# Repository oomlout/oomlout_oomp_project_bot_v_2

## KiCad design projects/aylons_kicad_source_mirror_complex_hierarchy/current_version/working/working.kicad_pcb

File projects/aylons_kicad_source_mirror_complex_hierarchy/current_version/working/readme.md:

# kicad_source_mirror
 
## summary 
* id: aylons_kicad_source_mirror_complex_hierarchy
* user: aylons
* name: kicad_source_mirror
* board: complex_hierarchy
* repo: https://github.com/aylons/kicad-source-mirror
* src_file_repo_kicad_pcb: qa/data/complex_hierarchy.kicad_pcb
* src_file_repo_kicad_pcb_link: https://github.com/aylons/kicad-source-mirror/tree/master/qa/data/complex_hierarchy.kicad_pcb

* src_file_repo_sch: helpers/tools_to_build_newstroke-font/font.sch
* src_file_repo_sch_link: https://github.com/aylons/kicad-source-mirror/tree/master/helpers/tools_to_build_newstroke-font/font.sch
* full details link: https://github.com/oomlout/oomlout_oomp_project_bot_v_2/tree/main/projects/aylons_kicad_source_mirror_complex_hierarchy/current_version/working

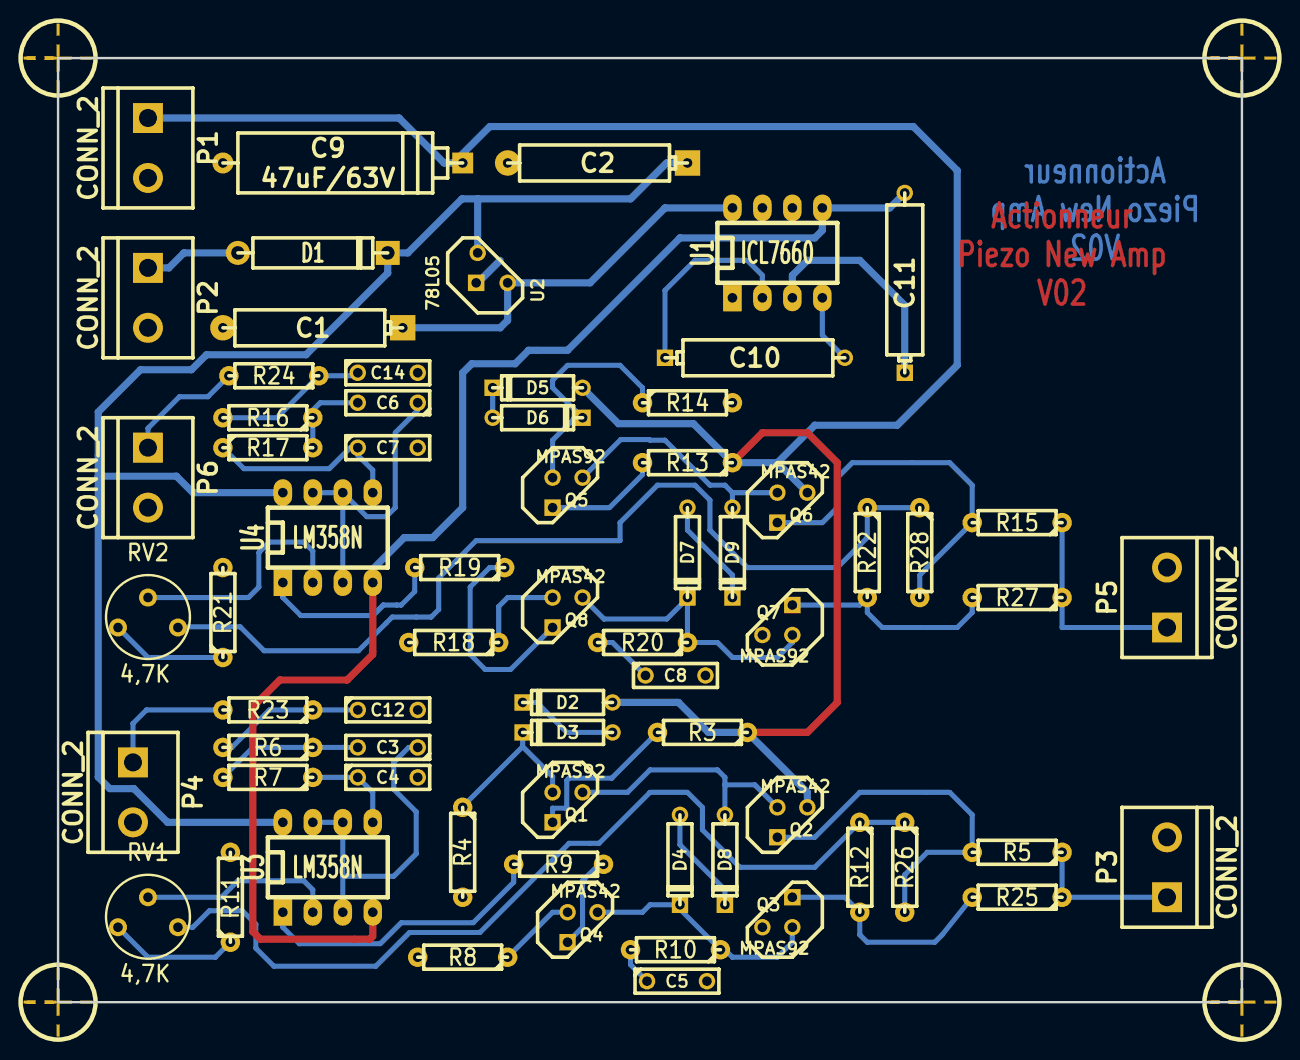
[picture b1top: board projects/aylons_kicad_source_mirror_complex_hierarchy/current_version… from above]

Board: 2 copper layers, 100.3 x 80.0 mm, 72 parts (0 on the bottom side), 50 nets.

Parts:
C1: 47uF; CP6
C2: 47uF/20V; CP6
C3, C6: 15nF; C2
C4, C7: 4,7nF; C2
C5, C8: 820pF; C2
C9: 47uF/63V; CP8
C10, C11: 10uF; CP6
C12, C14: 150nF; C2
D1: 1N4007; D5
D2, D3, D4, D5, D6, D7, D8, D9: 1N4148; D3
MIRE: *; MIRE
MIRE#2, MIRE#3, MIRE#4: *; MIRE
P1, P2, P3, P4, P5, P6: CONN_2; bornier2
Q1, Q3, Q5, Q7: MPAS92; TO92-CBE
Q2, Q4, Q6, Q8: MPAS42; TO92-CBE
R3, R13: 470; R3-LARGE_PADS
R4, R12, R14, R22, R26, R28: 220K; R3-LARGE_PADS
R5, R15, R25, R27: 47; R3-LARGE_PADS
R6, R7, R16, R17: 22K; R3-LARGE_PADS
R8, R9, R18, R19, R23, R24: 1K; R3-LARGE_PADS
R10, R20: 5,6K; R3-LARGE_PADS
R11, R21: 4,7K; R3-LARGE_PADS
RV1, RV2: 4,7K; RV2
U1: ICL7660; DIP-8__300_ELL
U2: 78L05; LM78LXX
U3, U4: LM358N; DIP-8__300_ELL

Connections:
+12V: C2.1, D1.2, U2.VI, U3.8, U4.8
-VAA: C11.2, U1.5, U3.4, U4.4
/12Vext: D1.1, P2.1
/ampli_h1: C3.1, U3.3, U3.6, U3.7
/ampli_h2: C6.1, U4.3, U4.6, U4.7
/ampli_h3: P3.1, R5.1, R25.1
/ampli_h4: P4.1, R23.2
/ampli_h5: P5.1, R15.1, R27.1
/ampli_h6: P6.1, R24.2
/ampli_h7: R12.1, R26.1, RV1.3
/ampli_h8: R22.1, R28.1, RV2.3
GND: C1.2, C2.2, C4.2, C5.2, C7.2, C8.2, C9.2, C11.1, C12.2, C14.2, P1.2, P2.2, P3.2, P4.2, P5.2, P6.2, Q3.C, Q7.C, R4.2, R8.2, R11.2, R14.2, R18.2, R21.2, U1.3, U2.GND
HT: C9.1, D2.1, D5.1, P1.1, Q2.C, Q6.C, R3.1, R13.1
unnamed: C10.2, U1.4
unnamed: C10.1, U1.2
unnamed: Q4.E, R9.1
unnamed: D2.2, D3.1
unnamed: C3.2, R6.1, R7.2
unnamed: C12.1, R6.2, R23.1
unnamed: C5.1, R10.2
unnamed: Q2.E, R5.2, R26.2
unnamed: Q3.E, R12.2, R25.2
unnamed: R11.1, RV1.1
unnamed: D3.2, Q1.B, R4.1
unnamed: Q4.B, R8.1
unnamed: R9.2, U3.1
unnamed: RV1.2, U3.2
unnamed: D4.1, D8.2
unnamed: C4.1, R7.1, U3.5
unnamed: D4.2, Q3.B, Q4.C, R10.1
unnamed: D8.1, Q1.C, Q2.B
unnamed: Q1.E, R3.2
unnamed: Q8.E, R19.1
unnamed: D5.2, D6.1
unnamed: C6.2, R16.1, R17.2
unnamed: C14.1, R16.2, R24.1
unnamed: C8.1, R20.2
unnamed: Q6.E, R15.2, R28.2
unnamed: Q7.E, R22.2, R27.2
unnamed: R21.1, RV2.1
unnamed: D6.2, Q5.B, R14.1
unnamed: Q8.B, R18.1
unnamed: R19.2, U4.1
unnamed: RV2.2, U4.2
unnamed: D7.1, D9.2
unnamed: C7.1, R17.1, U4.5
unnamed: D7.2, Q7.B, Q8.C, R20.1
unnamed: D9.1, Q5.C, Q6.B
unnamed: Q5.E, R13.2
VCC: C1.1, U1.8, U2.VO

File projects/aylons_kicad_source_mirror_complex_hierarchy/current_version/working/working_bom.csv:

"Id";"Designator";"Footprint";"Quantity";"Designation";"Supplier and ref";
1;"P1,P3,P2,P4,P5,P6";"bornier2";6;"CONN_2";;;
2;"C8,C5";"C2";2;"820pF";;;
3;"C4,C7";"C2";2;"4,7nF";;;
4;"C2";"CP6";1;"47uF/20V";;;
5;"C9";"CP8";1;"47uF/63V";;;
6;"C3,C6";"C2";2;"15nF";;;
7;"C1";"CP6";1;"47uF";;;
8;"D6,D4,D3,D2,D7,D5,D9,D8";"D3";8;"1N4148";;;
9;"D1";"D5";1;"1N4007";;;
10;"U2";"LM78LXX";1;"78L05";;;
11;"R12,R22,R4,R14,R26,R28";"R3-LARGE_PADS";6;"220K";;;
12;"R17,R6,R16,R7";"R3-LARGE_PADS";4;"22K";;;
13;"R3,R13";"R3-LARGE_PADS";2;"470";;;
14;"R18,R8,R19,R9,R23,R24";"R3-LARGE_PADS";6;"1K";;;
15;"R5,R15,R25,R27";"R3-LARGE_PADS";4;"47";;;
16;"R11,R21";"R3-LARGE_PADS";2;"4,7K";;;
17;"R10,R20";"R3-LARGE_PADS";2;"5,6K";;;
18;"Q3,Q5,Q7,Q1";"TO92-CBE";4;"MPAS92";;;
19;"Q6,Q2,Q4,Q8";"TO92-CBE";4;"MPAS42";;;
20;"U1";"DIP-8__300_ELL";1;"ICL7660";;;
21;"U4,U3";"DIP-8__300_ELL";2;"LM358N";;;
22;"RV1,RV2";"RV2";2;"4,7K";;;
23;"MIRE,MIRE,MIRE,MIRE";"MIRE";4;"*";;;
24;"C10,C11";"CP6";2;"10uF";;;
25;"C14,C12";"C2";2;"150nF";;;

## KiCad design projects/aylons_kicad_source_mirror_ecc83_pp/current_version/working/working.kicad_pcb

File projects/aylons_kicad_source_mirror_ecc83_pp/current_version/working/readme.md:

# kicad_source_mirror
 
## summary 
* id: aylons_kicad_source_mirror_ecc83_pp
* user: aylons
* name: kicad_source_mirror
* board: ecc83_pp
* repo: https://github.com/aylons/kicad-source-mirror
* src_file_repo_kicad_pcb: demos/ecc83/ecc83-pp.kicad_pcb
* src_file_repo_kicad_pcb_link: https://github.com/aylons/kicad-source-mirror/tree/master/demos/ecc83/ecc83-pp.kicad_pcb

* src_file_repo_sch: demos/ecc83/ecc83-pp.sch
* src_file_repo_sch_link: https://github.com/aylons/kicad-source-mirror/tree/master/demos/ecc83/ecc83-pp.sch
* full details link: https://github.com/oomlout/oomlout_oomp_project_bot_v_2/tree/main/projects/aylons_kicad_source_mirror_ecc83_pp/current_version/working

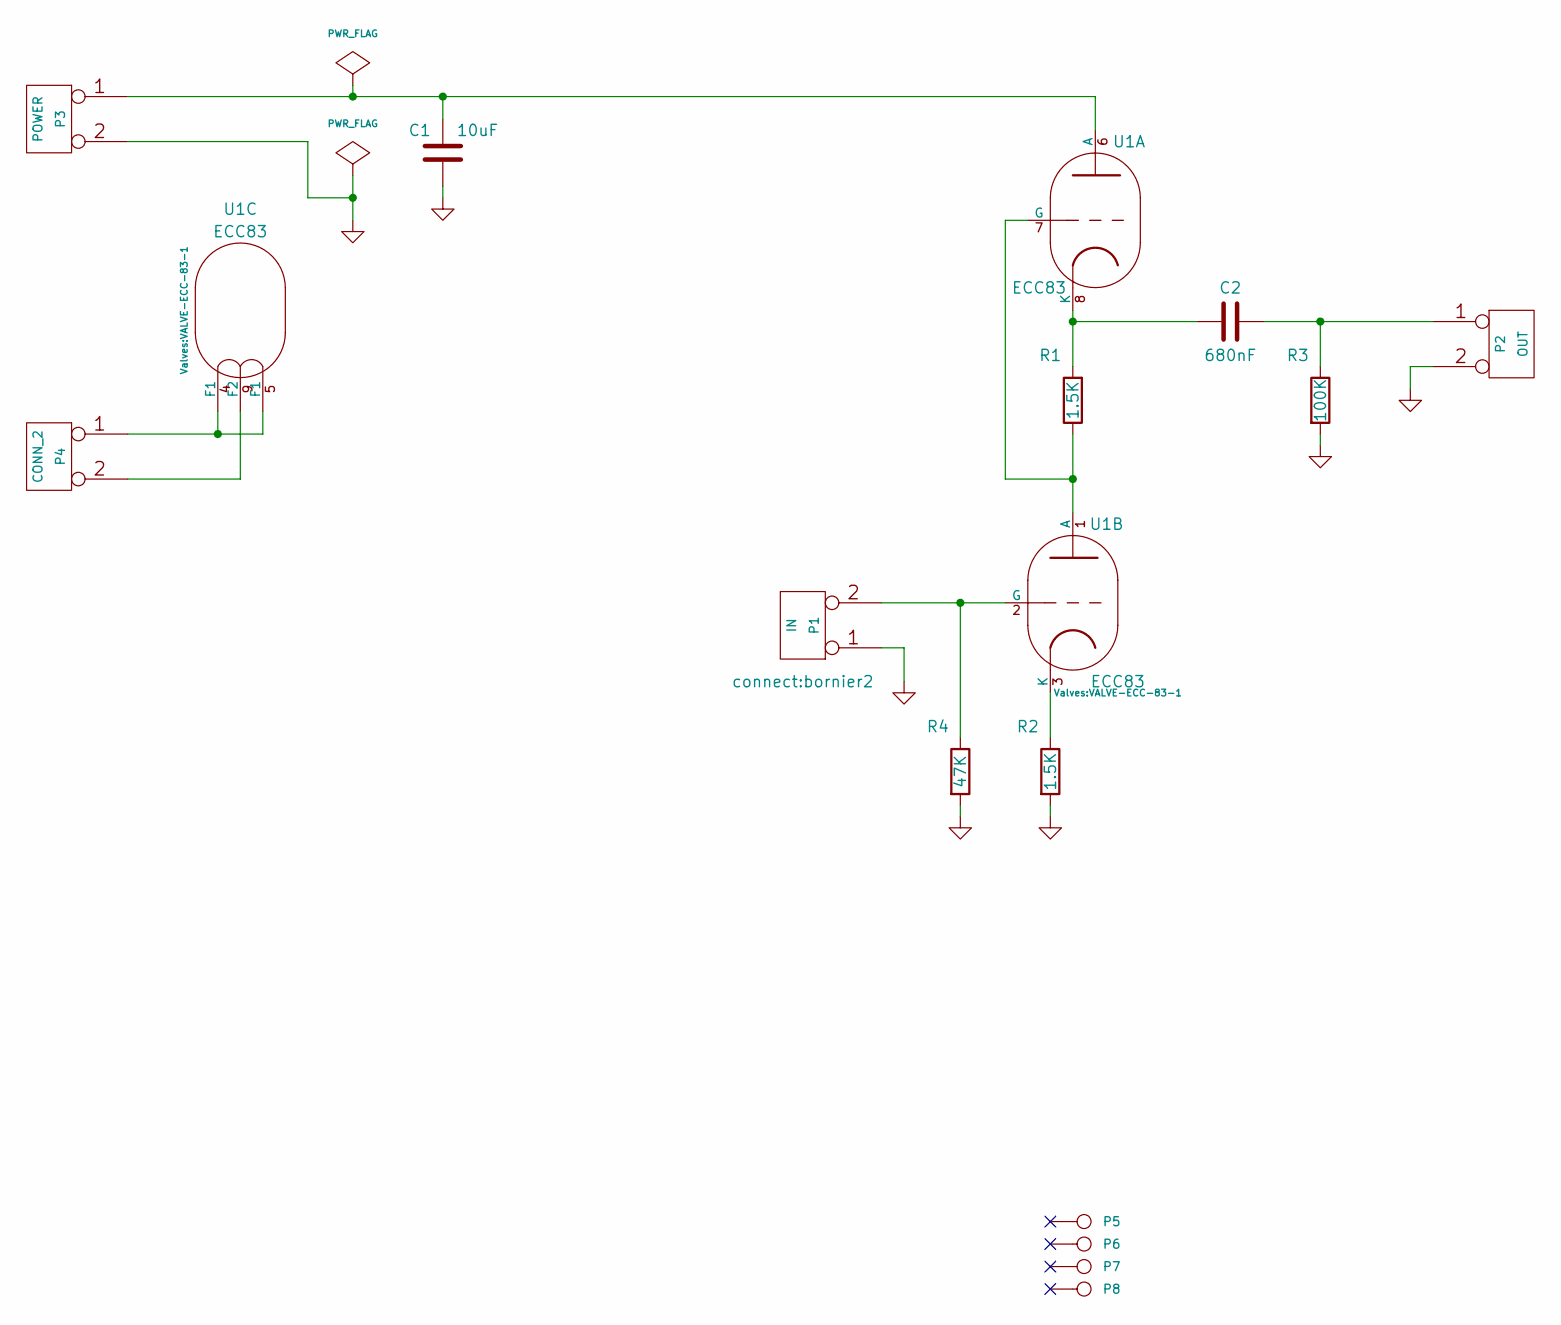
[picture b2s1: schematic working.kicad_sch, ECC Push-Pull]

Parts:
C1: 10uF; C2V10
C2: 680nF; C2
P1: IN; bornier2
P2: OUT; bornier2
P3: POWER; bornier2
P4: CONN_2; bornier2
P5, P6, P7, P8: CONN_1; 1pin
R1, R2: 1.5K; R3
R3: 100K; R3
R4: 47K; R3
U1: ECC83; VALVE-ECC-83-1

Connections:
GND: C1.2, P1.1, P2.2 (PM), P3.2 (PM), R2.2, R3.2, R4.2
unnamed: C1.1, P3.1, U1.6 (A)
unnamed: C2.1, P2.1, R3.1
unnamed: C2.2, R1.2, U1.8 (K)
unnamed: P1.2 (PM), R4.1, U1.2 (G)
unnamed: P4.1, U1.4 (F1), U1.5 (F1)
unnamed: P4.2 (PM), U1.9 (F2)
unnamed: R1.1, U1.1 (A), U1.7 (G)
unnamed: R2.1, U1.3 (K)

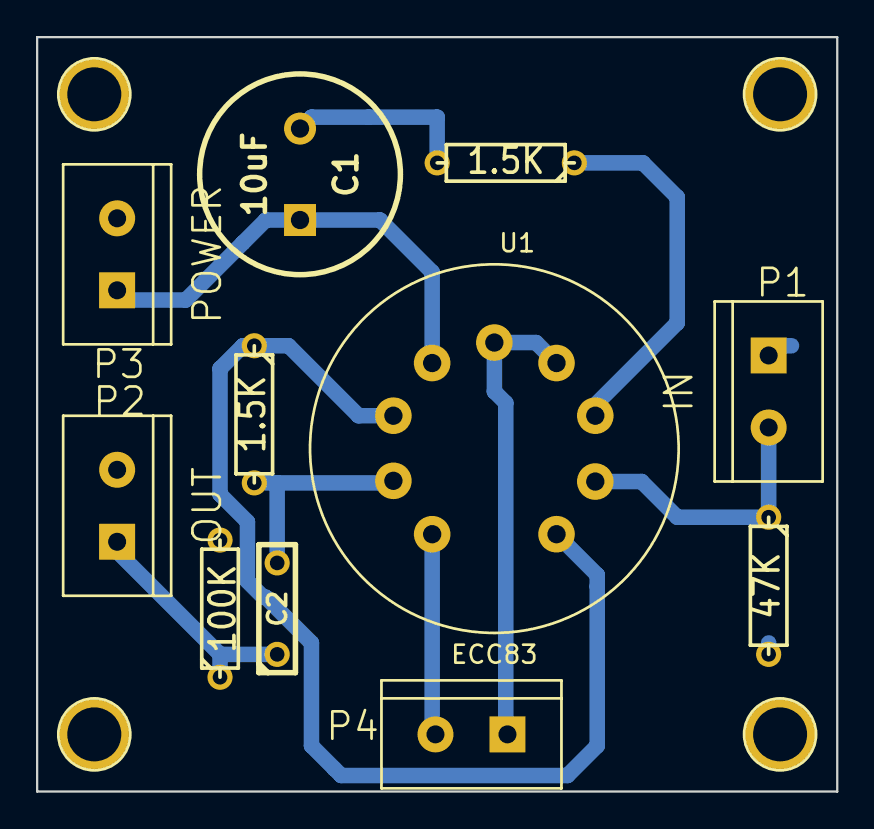
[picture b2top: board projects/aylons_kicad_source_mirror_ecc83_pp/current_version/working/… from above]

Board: 2 copper layers, 44.5 x 41.9 mm, 15 parts (0 on the bottom side), 9 nets.

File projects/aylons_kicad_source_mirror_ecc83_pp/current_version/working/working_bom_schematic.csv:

"Source:","C:\gh\oomlout_oomp_project_bot_v_2\projects\aylons_kicad_source_mirror_ecc83_pp\current_version\working\working.kicad_sch"
"Date:","27/09/2023 14:27:10"
"Tool:","Eeschema 7.0.6"
"Generator:","C:/Program Files/KiCad/7.0/bin/scripting/plugins/bom_csv_grouped_by_value_with_fp.py"
"Component Count:","15"
"Ref","Qnty","Value","Cmp name","Footprint","Description","Vendor","DNP"
"C1","1","10uF","C","discret:C2V10","","",""
"C2","1","680nF","C","discret:C2","","",""
"P1","1","IN","CONN_2","connect:bornier2","","",""
"P2","1","OUT","CONN_2","connect:bornier2","","",""
"P3","1","POWER","CONN_2","connect:bornier2","","",""
"P4","1","CONN_2","CONN_2","connect:bornier2","","",""
"P5, P6, P7, P8","4","CONN_1","CONN_1","connect:1pin","","",""
"R1, R2","2","1.5K","R","discret:R3","","",""
"R3","1","100K","R","discret:R3","","",""
"R4","1","47K","R","discret:R3","","",""
"U1","1","ECC83","ECC83","Valves:VALVE-ECC-83-1","","",""

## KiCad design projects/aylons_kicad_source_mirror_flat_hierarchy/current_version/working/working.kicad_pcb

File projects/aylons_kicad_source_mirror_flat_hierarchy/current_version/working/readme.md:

# kicad_source_mirror
 
## summary 
* id: aylons_kicad_source_mirror_flat_hierarchy
* user: aylons
* name: kicad_source_mirror
* board: flat_hierarchy
* repo: https://github.com/aylons/kicad-source-mirror
* src_file_repo_kicad_pcb: demos/flat_hierarchy/flat_hierarchy.kicad_pcb
* src_file_repo_kicad_pcb_link: https://github.com/aylons/kicad-source-mirror/tree/master/demos/flat_hierarchy/flat_hierarchy.kicad_pcb

* src_file_repo_sch: demos/flat_hierarchy/flat_hierarchy.sch
* src_file_repo_sch_link: https://github.com/aylons/kicad-source-mirror/tree/master/demos/flat_hierarchy/flat_hierarchy.sch
* full details link: https://github.com/oomlout/oomlout_oomp_project_bot_v_2/tree/main/projects/aylons_kicad_source_mirror_flat_hierarchy/current_version/working

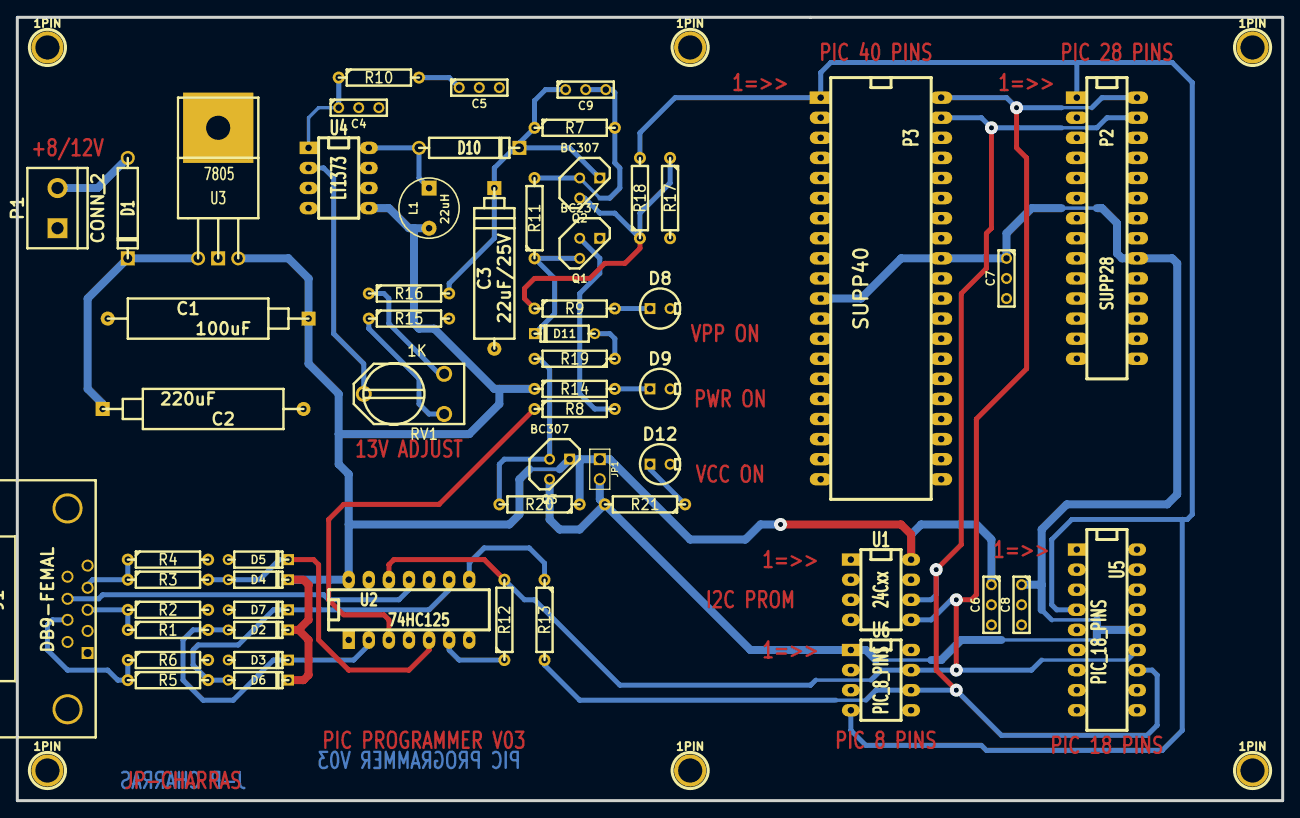
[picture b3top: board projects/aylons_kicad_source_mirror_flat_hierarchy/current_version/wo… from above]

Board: 2 copper layers, 160.0 x 99.1 mm, 64 parts (0 on the bottom side), 34 nets.

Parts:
1PIN, 1PIN#2, 1PIN#3, 1PIN#4, 1PIN#5, 1PIN#6: P***; 1pin
C1: 100uF; CP10
C2: 220uF; CP10
C3: 22uF/25V; CP8
C4: 0; C1-1
C5: 10nF; C1-1
C6, C7, C8: 100nF; C1-1
C9: 22OnF; C1-1
D1: 1N4004; D5
D2, D3, D4, D5, D6, D7, D11: BAT43; D3
D8: RED-LED; LEDV
D9: GREEN-LED; LEDV
D10: SCHOTTKY; D5
D12: YELLOW-LED; LEDV
J1: DB9-FEMAL; DB9FC
JP1: JUMPER; PIN_ARRAY_2X1
L1: 22uH; INDUCTOR_V
P1: CONN_2; bornier2
P2: SUPP28; 28DIP-ELL300
P3: SUPP40; 40DIP-ELL600
Q1: BC237; TO92
Q2, Q3: BC307; TO92
R1, R2, R3, R4, R5, R6, R7: 10K; R4
R8: 1K; R4
R9, R19, R20: 2.2K; R4
R10: 5,1K; R4
R11, R17: 22K; R4
R12, R13, R14, R21: 470; R4
R15: 6.2K; R4
R16: 62K; R4
R18: 220; R4
RV1: 1K; RV2X4
U1: 24Cxx; DIP-8__300_ELL
U2: 74HC125; DIP-14__300_ELL
U3: 7805; LM78XX
U4: LT1373; DIP-8__300_ELL
U5: PIC_18_PINS; DIP-18__300_ELL
U6: PIC_8_PINS; DIP-8__300_ELL

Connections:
/pic_programmer/CTS: J1.8, U2.11
/pic_programmer/DTR: J1.4, R3.1, R4.1
/pic_programmer/PC-CLOCK-OUT: J1.7, R5.1, R6.1
/pic_programmer/TXD: J1.3, R1.1, R2.1
CLOCK-RB6: P2.27, P3.39, R13.2, U1.6, U5.12, U6.6
DATA-RB7: P2.28, P3.40, R12.2, U1.5, U2.12, U5.13, U6.7
GND: C1.2, C2.2, C3.2, C4.2, C5.2, C6.2, C7.2, C8.2, D3.1, D5.1, D7.1, D8.2, D9.2, D12.2, J1.5, P1.1, P2.8, P2.19, P3.8, P3.12, P3.31, Q1.1, R2.2, R4.2, R6.2, R15.2, R17.2, U1.1, U1.2, U1.3, U1.4, U2.1, U2.4, U2.7, U2.10, U2.13, U3.GND, U4.6, U4.7, U5.5, U6.8
unnamed: C2.1, D1.2, U3.VI
unnamed: C4.1, R10.1, U4.1
unnamed: C5.1, R10.2
unnamed: C9.2, Q2.2, R7.2, R11.2
unnamed: D1.1, P1.2
unnamed: D2.1, D3.2, R1.2, U2.2
unnamed: D4.1, D5.2, R3.2, U2.5
unnamed: D6.1, D7.2, R5.2, U2.9
unnamed: D8.1, R9.2
unnamed: D9.1, R14.2
unnamed: D10.1, L1.1, U4.8
unnamed: D11.1, R19.1
unnamed: D11.2, Q1.3, R11.1
unnamed: D12.1, R21.1
unnamed: Q1.2, R8.2
unnamed: Q2.3, R9.1, R17.1, R18.1
unnamed: Q3.2, R19.2, R20.2
unnamed: R8.1, U2.3
unnamed: R12.1, U2.6
unnamed: R13.1, U2.8
unnamed: R15.1, RV1.1
unnamed: R16.1, RV1.3
unnamed: RV1.2, U4.2
VCC: C1.1, C6.1, D2.2, D4.2, D6.2, JP1.1, L1.2, Q3.1, R14.1, R20.1, U1.8, U2.14, U3.VO, U4.5
VCC_PIC: C7.1, C8.1, JP1.2, P2.20, P3.11, P3.32, Q3.3, R21.2, U5.14, U6.1
VPP: C3.1, C9.1, D10.2, Q2.1, R7.1, R16.2
VPP-MCLR: P2.1, P3.1, R18.2, U5.4, U6.4

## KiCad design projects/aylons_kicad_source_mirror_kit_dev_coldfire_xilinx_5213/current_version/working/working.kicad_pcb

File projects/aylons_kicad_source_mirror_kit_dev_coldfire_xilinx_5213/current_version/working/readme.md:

# kicad_source_mirror
 
## summary 
* id: aylons_kicad_source_mirror_kit_dev_coldfire_xilinx_5213
* user: aylons
* name: kicad_source_mirror
* board: kit_dev_coldfire_xilinx_5213
* repo: https://github.com/aylons/kicad-source-mirror
* src_file_repo_kicad_pcb: demos/kit-dev-coldfire-xilinx_5213/kit-dev-coldfire-xilinx_5213.kicad_pcb
* src_file_repo_kicad_pcb_link: https://github.com/aylons/kicad-source-mirror/tree/master/demos/kit-dev-coldfire-xilinx_5213/kit-dev-coldfire-xilinx_5213.kicad_pcb

* src_file_repo_sch: demos/interf_u/interf_u.sch
* src_file_repo_sch_link: https://github.com/aylons/kicad-source-mirror/tree/master/demos/interf_u/interf_u.sch
* full details link: https://github.com/oomlout/oomlout_oomp_project_bot_v_2/tree/main/projects/aylons_kicad_source_mirror_kit_dev_coldfire_xilinx_5213/current_version/working

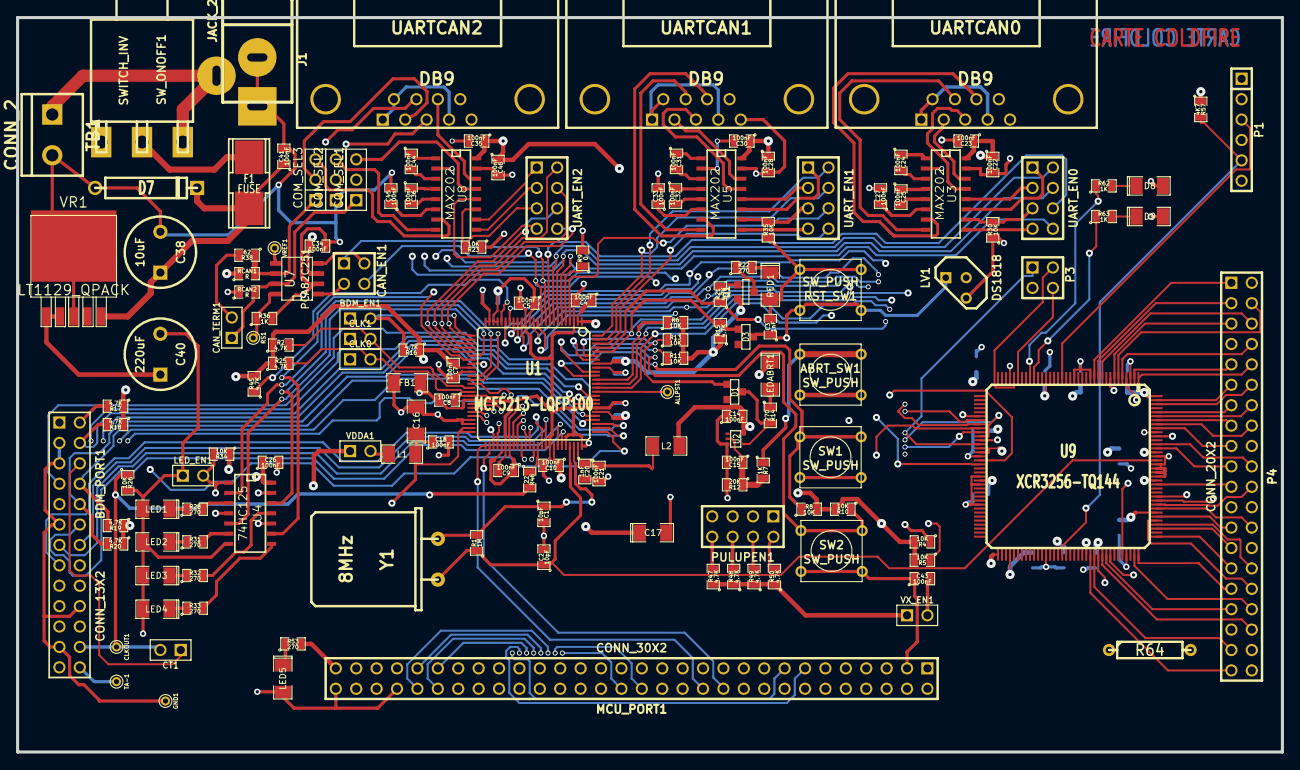
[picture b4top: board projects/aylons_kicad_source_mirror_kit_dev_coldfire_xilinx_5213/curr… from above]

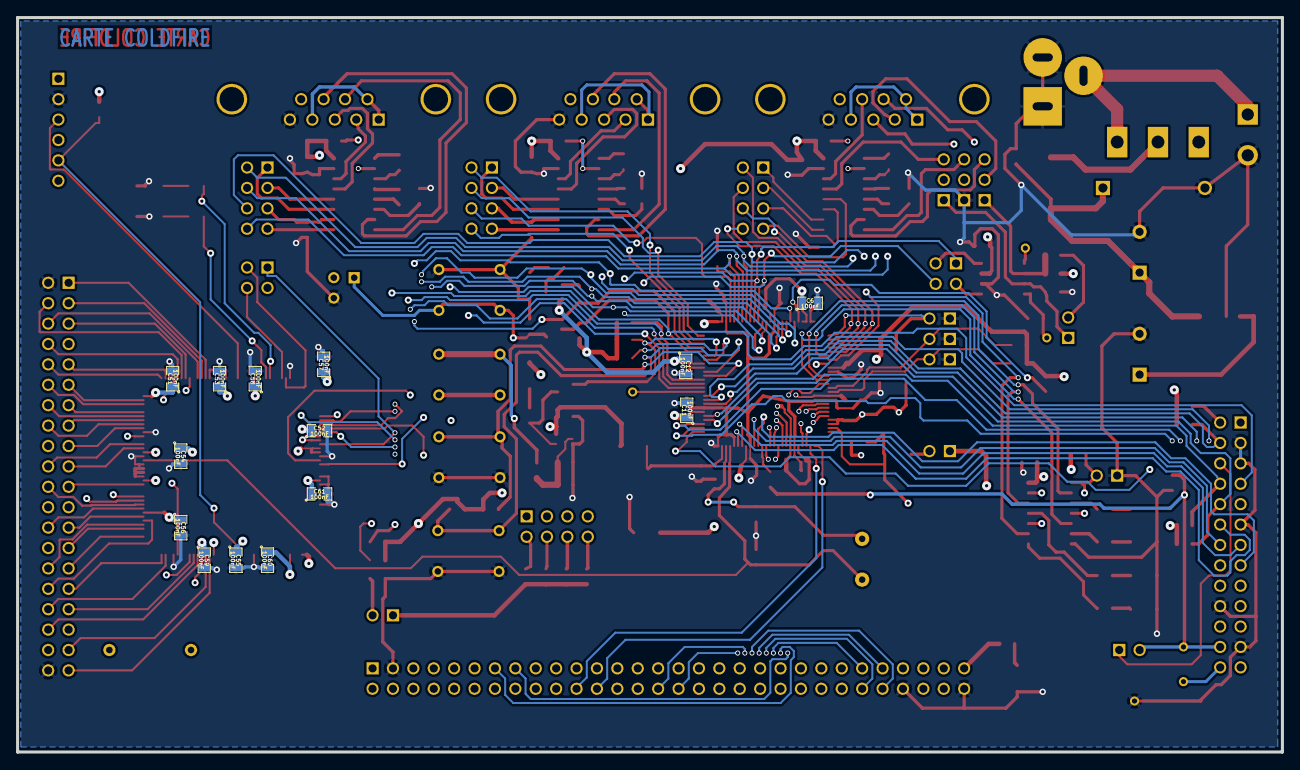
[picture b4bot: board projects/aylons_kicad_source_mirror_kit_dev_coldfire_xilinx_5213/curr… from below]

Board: 4 copper layers, 157.5 x 91.4 mm, 162 parts (14 on the bottom side), 209 nets.

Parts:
ABRT_SW1: SW_PUSH; SW_PUSH_SMALL
ALLPST1: CONN_1; PINTST
BDM_EN1: JUMPER; PIN_ARRAY_2X1
BDM_PORT1: CONN_13X2; pin_array_13x2
C1, C2: 10pF; SM0805
C3, C20: 1nF; SM0805
C4, C5, C6, C7, C8, C9, C10, C11, C12, C14, C15, C18, C21, C22, C23, C24, C25, C26, C27, C28, C30, C31, C32, C33, C34, C35, C36, C41, C43, C44, C45, C46, C51, C52, C53, C54, C55, C56, C57, C58, C59, C60, C61: 100nF; SM0805
C16: 10uF; SM1206POL
C17: 100uF; SM1206POL
C38: 10uF; C2V8
C40: 220uF; C2V8
CAN_EN1: CONN_2X2; PIN_ARRAY_2X2
CAN_TERM1: JUMPER; PIN_ARRAY_2X1
CLK0, CLK1: JUMPER; PIN_ARRAY_2X1
CLKOUT1: CONN_1; PINTST
COM_SEL1, COM_SEL2, COM_SEL3: CONN_3; PIN_ARRAY_3X1
CT1: JUMPER; PIN_ARRAY_2X1
D1, D3: BAT54; ST23AK#1
D7: 1N4004; D5
D8, D9: LED; SM1206POL
F1: FUSE; FSUPCMS
FB1: BEAD; SM1206
GND1: CONN_1; PINTST
J1: JACK_2P; JACK_ALIM
L1, L2: 10uH; SM1206
LED1, LED2, LED3, LED4, LED5: LED; SM1206POL
LEDABRT1: RED; SM1206POL
LED_EN1: JUMPER; PIN_ARRAY_2X1
LV1: DS1818; TO92-INVERT
MCU_PORT1: CONN_30X2; PIN_ARRAY_30X2
P1: CONN_6; PIN_ARRAY-6X1
P3: CONN_2X2; PIN_ARRAY_2X2
P4: CONN_20X2; PIN_ARRAY_20X2
PULUPEN1: CONN_4X2; pin_array_4x2
Q1: 3906; SOT23EBC
R1: 1M; SM0805
R2, R15, R16, R17, R18, R19, R20, R21, R25, R45, R47, R48, R49, R50: 4,7K; SM0805
R4, R5, R6, R8, R10, R11, R13, R23, R26, R30, R34, R35: 10K; SM0805
R7, R36, R62, R63: 1K; SM0805
R9: 0; SM0805
R12: 20K; SM0805
R14, R22, R28, R31, R32, R33, R53: 270; SM0805
R38: 62; SM0805
R46: 22; SM0805
R57: 4K7; SM0805
R64: 3,3; R4
RCAN1, RCAN2: R; SM0805
RED1: LED_RESET1; SM1206POL
RS1: CONN_1; PINTST
RST_SW1: SW_PUSH; SW_PUSH_SMALL
SW1, SW2: SW_PUSH; SW_PUSH_SMALL
SW_ONOFF1: SWITCH_INV; SW_SPDT
TA-1: CONN_1; PINTST
TB1: CONN_2; bornier2
U1: MCF5213-LQFP100; VQFP100
U2: 74AHC1G14; SOT353
U3, U5, U8: MAX202; SO16E
U4: 74HC125; SO14E
U7: PCA82C251; SO8E
U9: XCR3256-TQ144; TQFP144
UARTCAN0, UARTCAN1, UARTCAN2: DB9; DB9FC
UART_EN0, UART_EN1, UART_EN2: CONN_4X2; pin_array_4x2
VDDA1: JUMPER; PIN_ARRAY_2X1
VR1: LT1129_QPACK; DPAK5
VREF1: CONN_1; PINTST
VX_EN1: JUMPER; PIN_ARRAY_2X1
Y1: 8MHz; HC-18UH

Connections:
/ALLPST: ALLPST1.1, U1.86
/AN0: MCU_PORT1.10, U1.43
/AN1: MCU_PORT1.12, U1.44
/AN2: MCU_PORT1.14, U1.45
/AN3: MCU_PORT1.16, U1.46
/AN4: MCU_PORT1.18, U1.54
/AN5: MCU_PORT1.20, U1.53
/AN6: MCU_PORT1.22, U1.52
/AN7: MCU_PORT1.24, U1.51
/BKPT-: BDM_PORT1.2, R17.2, U1.76
/CLKIN/EXTAL: C1.1, R1.2, U1.73, Y1.1
/CLKMOD0: CLK0.2, R25.2, U1.40
/CLKMOD1: CLK1.2, R2.2, U1.39
/DDAT0: BDM_PORT1.19, U1.77
/DDAT1: BDM_PORT1.18, U1.78
/DDAT2: BDM_PORT1.17, U1.83
/DDAT3: BDM_PORT1.16, U1.84
/DSCLK: BDM_PORT1.4, R18.2, U1.85
/DSI: BDM_PORT1.8, R19.2, U1.79
/DSO: BDM_PORT1.10, R20.2, U1.80
/DTIN0: MCU_PORT1.34, U1.36, U4.2
/DTIN1: MCU_PORT1.36, U1.37, U4.5
/DTIN2: MCU_PORT1.38, U1.31, U4.12
/DTIN3: MCU_PORT1.40, U1.32, U4.9
/GPT0: MCU_PORT1.49, U1.58
/GPT1: MCU_PORT1.50, U1.59
/GPT2: MCU_PORT1.51, U1.61
/GPT3: MCU_PORT1.52, U1.62
/IRQ-4: MCU_PORT1.33, R8.1, SW1.1, U1.90
/IRQ-5: MCU_PORT1.35, R10.1, SW2.1, U1.91
/IRQ-6: MCU_PORT1.37, R11.1, U1.94
/IRQ-7: D1.1, MCU_PORT1.39, R13.1, U1.95
/JTAG_EN: BDM_EN1.2, R16.2, U1.26
/PST0: BDM_PORT1.15, U1.65
/PST1: BDM_PORT1.14, U1.66
/PST2: BDM_PORT1.13, U1.69
/PST3: BDM_PORT1.12, U1.70
/QSPI_CS0: MCU_PORT1.23, PULUPEN1.3, U1.20
/QSPI_CS3: MCU_PORT1.29, U1.12
/TCLK: BDM_PORT1.24, CLKOUT1.1, CT1.2, R26.1, R46.2
/VDDPLL: C20.1, C21.1, L2.2, U1.74
/inout_user/CANRX: CAN_EN1.4, MCU_PORT1.28, PULUPEN1.7, U1.11
/inout_user/CANTX: CAN_EN1.1, MCU_PORT1.26, PULUPEN1.5, U1.10
/inout_user/CAN_H: CAN_TERM1.1, COM_SEL1.1, RCAN2.2, U7.7
/inout_user/CAN_L: COM_SEL3.1, R38.1, RCAN1.2, U7.6
/inout_user/CTS0: U3.8, UARTCAN0.7
/inout_user/CTS1: U5.8, UARTCAN1.7
/inout_user/CTS2/CANH: COM_SEL1.2, UARTCAN2.7
/inout_user/PWM1: MCU_PORT1.13, U1.38
/inout_user/PWM3: MCU_PORT1.15, U1.33
/inout_user/PWM5: MCU_PORT1.30, U1.60
/inout_user/PWM7: MCU_PORT1.32, U1.63
/inout_user/QSPI_DIN: MCU_PORT1.19, U1.16, U9.46
/inout_user/QSPI_DOUT: MCU_PORT1.17, U1.17, U9.47
/inout_user/QSPI_SCLK: MCU_PORT1.21, PULUPEN1.1, U1.18, U9.48
/inout_user/RCON-: MCU_PORT1.53, R45.1, U1.21
/inout_user/RSTI-: BDM_PORT1.7, D3.1, MCU_PORT1.6, R15.2, U1.96
/inout_user/RTS0: U3.7, UARTCAN0.8
/inout_user/RTS0-: MCU_PORT1.4, R21.1, U1.97
/inout_user/RTS1: U5.7, UARTCAN1.8
/inout_user/RTS2: U8.14, UARTCAN2.8
/inout_user/RXD0: U3.13, UARTCAN0.3
/inout_user/RXD1: U5.13, UARTCAN1.3
/inout_user/RXD2: COM_SEL2.2, UARTCAN2.3
/inout_user/RxD_CAN: CAN_EN1.2, U7.4
/inout_user/TXD0: U3.14, UARTCAN0.2
/inout_user/TXD1: U5.14, UARTCAN1.2
/inout_user/TXD2/CANL: COM_SEL3.2, UARTCAN2.2
/inout_user/TxD_CAN: CAN_EN1.3, U7.1
/inout_user/UCTS0: MCU_PORT1.44, U1.6, UART_EN0.8
/inout_user/UCTS1: MCU_PORT1.11, P3.1, U1.98, U9.49, UART_EN1.8
/inout_user/UCTS2: MCU_PORT1.48, U1.27, UART_EN2.8
/inout_user/URTS0: MCU_PORT1.42, U1.9, UART_EN0.6
/inout_user/URTS1: MCU_PORT1.9, P3.3, U1.4, U9.53, UART_EN1.6
/inout_user/URTS2: MCU_PORT1.46, U1.30, UART_EN2.6
/inout_user/URXD0: MCU_PORT1.43, U1.7, UART_EN0.4
/inout_user/URXD1: MCU_PORT1.7, U1.100, UART_EN1.4
/inout_user/URXD2: MCU_PORT1.47, U1.28, UART_EN2.4
/inout_user/UTXD0: MCU_PORT1.41, U1.8, UART_EN0.2
/inout_user/UTXD1: MCU_PORT1.5, U1.99, UART_EN1.2
/inout_user/UTXD2: MCU_PORT1.45, U1.29, UART_EN2.2
/inout_user/VCCA: C16.1, C18.1, L1.2, MCU_PORT1.55, MCU_PORT1.57, U1.49, U1.50
/xilinx/+3,3V_OUT: P4.38, R64.2
/xilinx/GLCK2: C2.1, R1.1, U1.72, U9.128, Y1.2
/xilinx/IRQ-1: MCU_PORT1.2, R4.1, U1.87, U9.42
/xilinx/IRQ-2: MCU_PORT1.8, R5.1, U1.88, U9.43
/xilinx/IRQ-3: MCU_PORT1.31, R6.1, U1.89, U9.44
/xilinx/LED_TEST1: R62.1, U9.28
/xilinx/LED_TEST2: R63.1, U9.27
/xilinx/QSPI_CS1: MCU_PORT1.25, U1.19, U9.54
/xilinx/QSPI_CS2: MCU_PORT1.27, U1.13, U9.45
/xilinx/TCK: P1.5, R57.2, U9.89
/xilinx/TDI: P1.4, U9.4
/xilinx/TDO: P1.6, U9.104
/xilinx/TMS: P1.3, U9.20
/xilinx/XIL_D0: P4.1, U9.12
/xilinx/XIL_D1: P4.3, U9.11
/xilinx/XIL_D2: P4.5, U9.7
/xilinx/XIL_D3: P4.7, U9.8
/xilinx/XIL_D4: P4.9, U9.2
/xilinx/XIL_D5: P4.11, U9.143
/xilinx/XIL_D6: P4.13, U9.140
/xilinx/XIL_D7: P4.15, U9.138
/xilinx/XIL_D8: P4.17, U9.136
/xilinx/XIL_D9: P4.19, U9.131
/xilinx/XIL_D10: P4.21, U9.122
/xilinx/XIL_D11: P4.23, U9.119
/xilinx/XIL_D12: P4.25, U9.114
/xilinx/XIL_D13: P4.27, U9.111
/xilinx/XIL_D14: P4.29, U9.109
/xilinx/XIL_D15: P4.31, U9.108
/xilinx/XIL_D16: P4.33, U9.100
/xilinx/XIL_D17: P4.35, U9.101
/xilinx/XIL_D18: P4.37, U9.97
/xilinx/XIL_D19: P4.39, U9.96
/xilinx/XIL_D20: P4.4, U9.6
/xilinx/XIL_D21: P4.6, U9.10
/xilinx/XIL_D22: P4.8, U9.5
/xilinx/XIL_D23: P4.10, U9.1
/xilinx/XIL_D24: P4.12, U9.142
/xilinx/XIL_D25: P4.14, U9.139
/xilinx/XIL_D26: P4.16, U9.137
/xilinx/XIL_D27: P4.18, U9.134
/xilinx/XIL_D28: P4.20, U9.132
/xilinx/XIL_D29: P4.22, U9.117
/xilinx/XIL_D30: P4.24, U9.118
/xilinx/XIL_D31: P4.26, U9.116
/xilinx/XIL_D32: P4.28, U9.98
/xilinx/XIL_D33: P4.30, U9.112
/xilinx/XIL_D34: P4.32, U9.113
/xilinx/XIL_D35: P4.34, U9.107
/xilinx/XIL_D36: P4.36, U9.99
GND: BDM_EN1.1, BDM_PORT1.3, BDM_PORT1.5, BDM_PORT1.11, BDM_PORT1.20, BDM_PORT1.23, C1.2, C2.2, C3.2, C4.2, C5.2, C6.2, C7.2, C8.2, C9.2, C10.2, C11.2, C12.2, C14.1, C15.2, C17.2, C20.2, C21.2, C22.2, C26.2, C27.2, C28.2, C33.2, C34.2, C38.2, C40.2, C41.2, C43.1, C45.2, C46.2, C51.2, C52.2, C53.2, C54.2, C55.2, C56.2, C57.2, C58.2, C59.2, C60.2, C61.2, CLK0.1, CLK1.1, COM_SEL2.1, D7.1, D8.2, D9.2, FB1.1, GND1.1, J1.1, J1.2, LED1.2, LED2.2, LED3.2, LED4.2, LED5.2, LED_EN1.1, LV1.3, MCU_PORT1.3, MCU_PORT1.54, MCU_PORT1.60, P1.2, P4.2, P4.40, R9.2, R12.2, R23.1, R26.2, R30.1, R35.1, R36.2, RCAN2.1, RED1.2, RST_SW1.2, SW1.2, SW2.2, TB1.2, U1.3, U1.15, U1.24, U1.25, U1.35, U1.42, U1.56, U1.67, U1.71, U1.75, U1.82, U1.92, U2.3, U3.15, U4.7, U5.15, U7.2, U8.15, U9.3, U9.13, U9.17, U9.33, U9.52, U9.57, U9.59, U9.64, U9.85, U9.105, U9.124, U9.125, U9.126, U9.127, U9.129, U9.135, UARTCAN0.5, UARTCAN1.5, UARTCAN2.5, VR1.3
GNDA: C16.2, C18.2, FB1.2, MCU_PORT1.56, MCU_PORT1.58, U1.47, U1.48
unnamed: ABRT_SW1.1, R7.1
unnamed: BDM_PORT1.6, CT1.1
unnamed: BDM_PORT1.26, TA-1.1
unnamed: C3.1, D3.2, LV1.1, RST_SW1.1
unnamed: C15.1, R7.2, R12.1, U2.2
unnamed: C23.2, U3.2
unnamed: C24.1, U3.1
unnamed: C24.2, U3.3
unnamed: C25.1, U3.4
unnamed: C25.2, U3.5
unnamed: C27.1, U3.6
unnamed: C30.2, U5.2
unnamed: C31.1, U5.1
unnamed: C31.2, U5.3
unnamed: C32.1, U5.4
unnamed: C32.2, U5.5
unnamed: C33.1, U5.6
unnamed: C35.2, U8.2
unnamed: C36.1, U8.4
unnamed: C36.2, U8.5
unnamed: C38.1, C41.1, D7.2, F1.2, VR1.5
unnamed: C43.2, MCU_PORT1.1, VX_EN1.2
unnamed: C44.1, U8.1
unnamed: C44.2, U8.3
unnamed: C45.1, U8.6
unnamed: CAN_TERM1.2, R38.2
unnamed: COM_SEL1.3, U8.13
unnamed: COM_SEL2.3, U8.8
unnamed: COM_SEL3.3, U8.7
unnamed: D1.2, R14.2, U2.4
unnamed: D8.1, R62.2
unnamed: D9.1, R63.2
unnamed: F1.1, SW_ONOFF1.2
unnamed: J1.3, SW_ONOFF1.3, TB1.1
unnamed: L1.1, VDDA1.2
unnamed: LED1.1, R28.1
unnamed: LED2.1, R31.1
unnamed: LED3.1, R32.1
unnamed: LED4.1, R33.1
unnamed: LED5.1, R53.1
unnamed: LEDABRT1.2, R14.1
unnamed: LED_EN1.2, R34.2, U4.1, U4.4, U4.10, U4.13
unnamed: P3.2, U9.32
unnamed: P3.4, U9.31
unnamed: PULUPEN1.2, R50.2
unnamed: PULUPEN1.4, R49.2
unnamed: PULUPEN1.6, R48.2
unnamed: PULUPEN1.8, R47.2
unnamed: Q1.2, R21.2
unnamed: Q1.3, R22.1
unnamed: R9.1, U1.5
unnamed: R22.2, RED1.1
unnamed: R23.2, U8.11, UART_EN2.5
unnamed: R28.2, U4.3
unnamed: R30.2, U3.10, UART_EN0.5
unnamed: R31.2, U4.6
unnamed: R32.2, U4.11
unnamed: R33.2, U4.8
unnamed: R35.2, U5.10, UART_EN1.5
unnamed: R36.1, RS1.1, U7.8
unnamed: R46.1, U1.64
unnamed: U3.9, UART_EN0.7
unnamed: U3.11, UART_EN0.1
unnamed: U3.12, UART_EN0.3
unnamed: U5.9, UART_EN1.7
unnamed: U5.11, UART_EN1.1
unnamed: U5.12, UART_EN1.3
unnamed: U7.5, VREF1.1
unnamed: U8.9, UART_EN2.3
unnamed: U8.10, UART_EN2.1
unnamed: U8.12, UART_EN2.7
unnamed: UARTCAN0.1, UARTCAN0.4, UARTCAN0.6
unnamed: UARTCAN1.1, UARTCAN1.4, UARTCAN1.6
unnamed: UARTCAN2.1, UARTCAN2.4, UARTCAN2.6
VDD: ABRT_SW1.2, BDM_PORT1.9, BDM_PORT1.25, C4.1, C5.1, C6.1, C7.1, C8.1, C9.1, C10.1, C11.1, C12.1, C14.2, C17.1, C22.1, C23.1, C26.1, C28.1, C30.1, C34.1, C35.1, C40.1, C46.1, C51.1, C52.1, C53.1, C54.1, C55.1, C56.1, C57.1, C58.1, C59.1, C60.1, C61.1, L2.1, LEDABRT1.1, LV1.2, MCU_PORT1.59, P1.1, Q1.1, R2.1, R4.2, R5.2, R6.2, R8.2, R10.2, R11.2, R13.2, R15.1, R16.1, R17.1, R18.1, R19.1, R20.1, R25.1, R34.1, R45.2, R47.1, R48.1, R49.1, R50.1, R53.2, R57.1, R64.1, RCAN1.1, U1.1, U1.2, U1.14, U1.22, U1.23, U1.34, U1.41, U1.55, U1.57, U1.68, U1.81, U1.93, U2.5, U3.16, U4.14, U5.16, U7.3, U8.16, U9.24, U9.50, U9.51, U9.58, U9.73, U9.76, U9.95, U9.115, U9.123, U9.130, U9.144, VDDA1.1, VR1.1, VR1.2, VX_EN1.1

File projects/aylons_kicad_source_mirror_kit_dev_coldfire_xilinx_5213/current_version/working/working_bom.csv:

"Id";"Designator";"Footprint";"Quantity";"Designation";"Supplier and ref";
1;"ABRT_SW1,RST_SW1,SW1,SW2";"SW_PUSH_SMALL";4;"SW_PUSH";;;
2;"ALLPST1,CLKOUT1,GND1,RS1,TA-1,VREF1";"PINTST";6;"CONN_1";;;
3;"BDM_EN1,CAN_TERM1,CLK0,CLK1,CT1,LED_EN1,VDDA1,VX_EN1";"PIN_ARRAY_2X1";8;"JUMPER";;;
4;"BDM_PORT1";"pin_array_13x2";1;"CONN_13X2";;;
5;"C1,C2";"SM0805";2;"10pF";;;
6;"C3,C20";"SM0805";2;"1nF";;;
7;"C4,C5,C7,C8,C9,C10,C14,C15,C18,C21,C22,C23,C24,C25,C26,C27,C28,C30,C31,C32,C33,C34,C35,C36,C41,C43,C44,C45,C46,C6,C11,C12,C51,C52,C53,C54,C55,C56,C57,C58,C59,C60,C61";"SM0805";43;"100nF";;;
8;"C16";"SM1206POL";1;"10uF";;;
9;"C17";"SM1206POL";1;"100uF";;;
10;"C38";"C2V8";1;"10uF";;;
11;"C40";"C2V8";1;"220uF";;;
12;"CAN_EN1,P3";"PIN_ARRAY_2X2";2;"CONN_2X2";;;
13;"COM_SEL1,COM_SEL2,COM_SEL3";"PIN_ARRAY_3X1";3;"CONN_3";;;
14;"D1,D3";"ST23AK#1";2;"BAT54";;;
15;"D7";"D5";1;"1N4004";;;
16;"D8,D9,LED1,LED2,LED3,LED4,LED5";"SM1206POL";7;"LED";;;
17;"F1";"FSUPCMS";1;"FUSE";;;
18;"FB1";"SM1206";1;"BEAD";;;
19;"J1";"JACK_ALIM";1;"JACK_2P";;;
20;"L1,L2";"SM1206";2;"10uH";;;
21;"LEDABRT1";"SM1206POL";1;"RED";;;
22;"LV1";"TO92-INVERT";1;"DS1818";;;
23;"MCU_PORT1";"PIN_ARRAY_30X2";1;"CONN_30X2";;;
24;"P1";"PIN_ARRAY-6X1";1;"CONN_6";;;
25;"P4";"PIN_ARRAY_20X2";1;"CONN_20X2";;;
26;"PULUPEN1,UART_EN0,UART_EN1,UART_EN2";"pin_array_4x2";4;"CONN_4X2";;;
27;"Q1";"SOT23EBC";1;"3906";;;
28;"R1";"SM0805";1;"1M";;;
29;"R2,R15,R16,R17,R18,R19,R20,R21,R25,R45,R47,R48,R49,R50";"SM0805";14;"4,7K";;;
30;"R4,R5,R6,R8,R10,R11,R13,R23,R26,R30,R34,R35";"SM0805";12;"10K";;;
31;"R7,R36,R62,R63";"SM0805";4;"1K";;;
32;"R9";"SM0805";1;"0";;;
33;"R12";"SM0805";1;"20K";;;
34;"R14,R22,R28,R31,R32,R33,R53";"SM0805";7;"270";;;
35;"R38";"SM0805";1;"62";;;
36;"R46";"SM0805";1;"22";;;
37;"R57";"SM0805";1;"4K7";;;
38;"R64";"R4";1;"3,3";;;
39;"RCAN1,RCAN2";"SM0805";2;"R";;;
40;"RED1";"SM1206POL";1;"LED_RESET1";;;
41;"SW_ONOFF1";"SW_SPDT";1;"SWITCH_INV";;;
42;"TB1";"bornier2";1;"CONN_2";;;
43;"U1";"VQFP100";1;"MCF5213-LQFP100";;;
44;"U2";"SOT353";1;"74AHC1G14";;;
45;"U3,U5,U8";"SO16E";3;"MAX202";;;
46;"U4";"SO14E";1;"74HC125";;;
47;"U7";"SO8E";1;"PCA82C251";;;
48;"U9";"TQFP144";1;"XCR3256-TQ144";;;
49;"UARTCAN0,UARTCAN1,UARTCAN2";"DB9FC";3;"DB9";;;
50;"VR1";"DPAK5";1;"LT1129_QPACK";;;
51;"Y1";"HC-18UH";1;"8MHz";;;
